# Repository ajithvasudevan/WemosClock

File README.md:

## Wemos Clock

This clock is based on the Wemos D1 Mini MCU and it keeps accurate time using NTP servers over the internet, just like regular computers.

### Schematic Diagram

### Parts List
1. 7-Segment Display units (2.3 inch high for this PCB design, otherwise, could be any size) - 4 Nos
2. Wemos D1 Mini - 1 No
3. General purpose NPN transistors (E.g., 2N 2222A)  - 11 Nos
4. General purpose PNP transistors (E.g., 2N 2907A)  - 4 Nos
5. Resistors - 2k2 Ω   - 21 Nos
6. Resistors - 220 Ω   -  7 Nos
7. 12V DC 5W Power supply module HLK-5M12 - 1 No
8. 5V Regulator IC 7805 - 1 No
9. Capacitor 470 μF  - No
10. PCB fabricated to the specifications [here](KiCAD/WemosClock.kicad_pcb)

### PCB

### PCB (3-D Model - component side)

### PCB (3-D Model - display side)

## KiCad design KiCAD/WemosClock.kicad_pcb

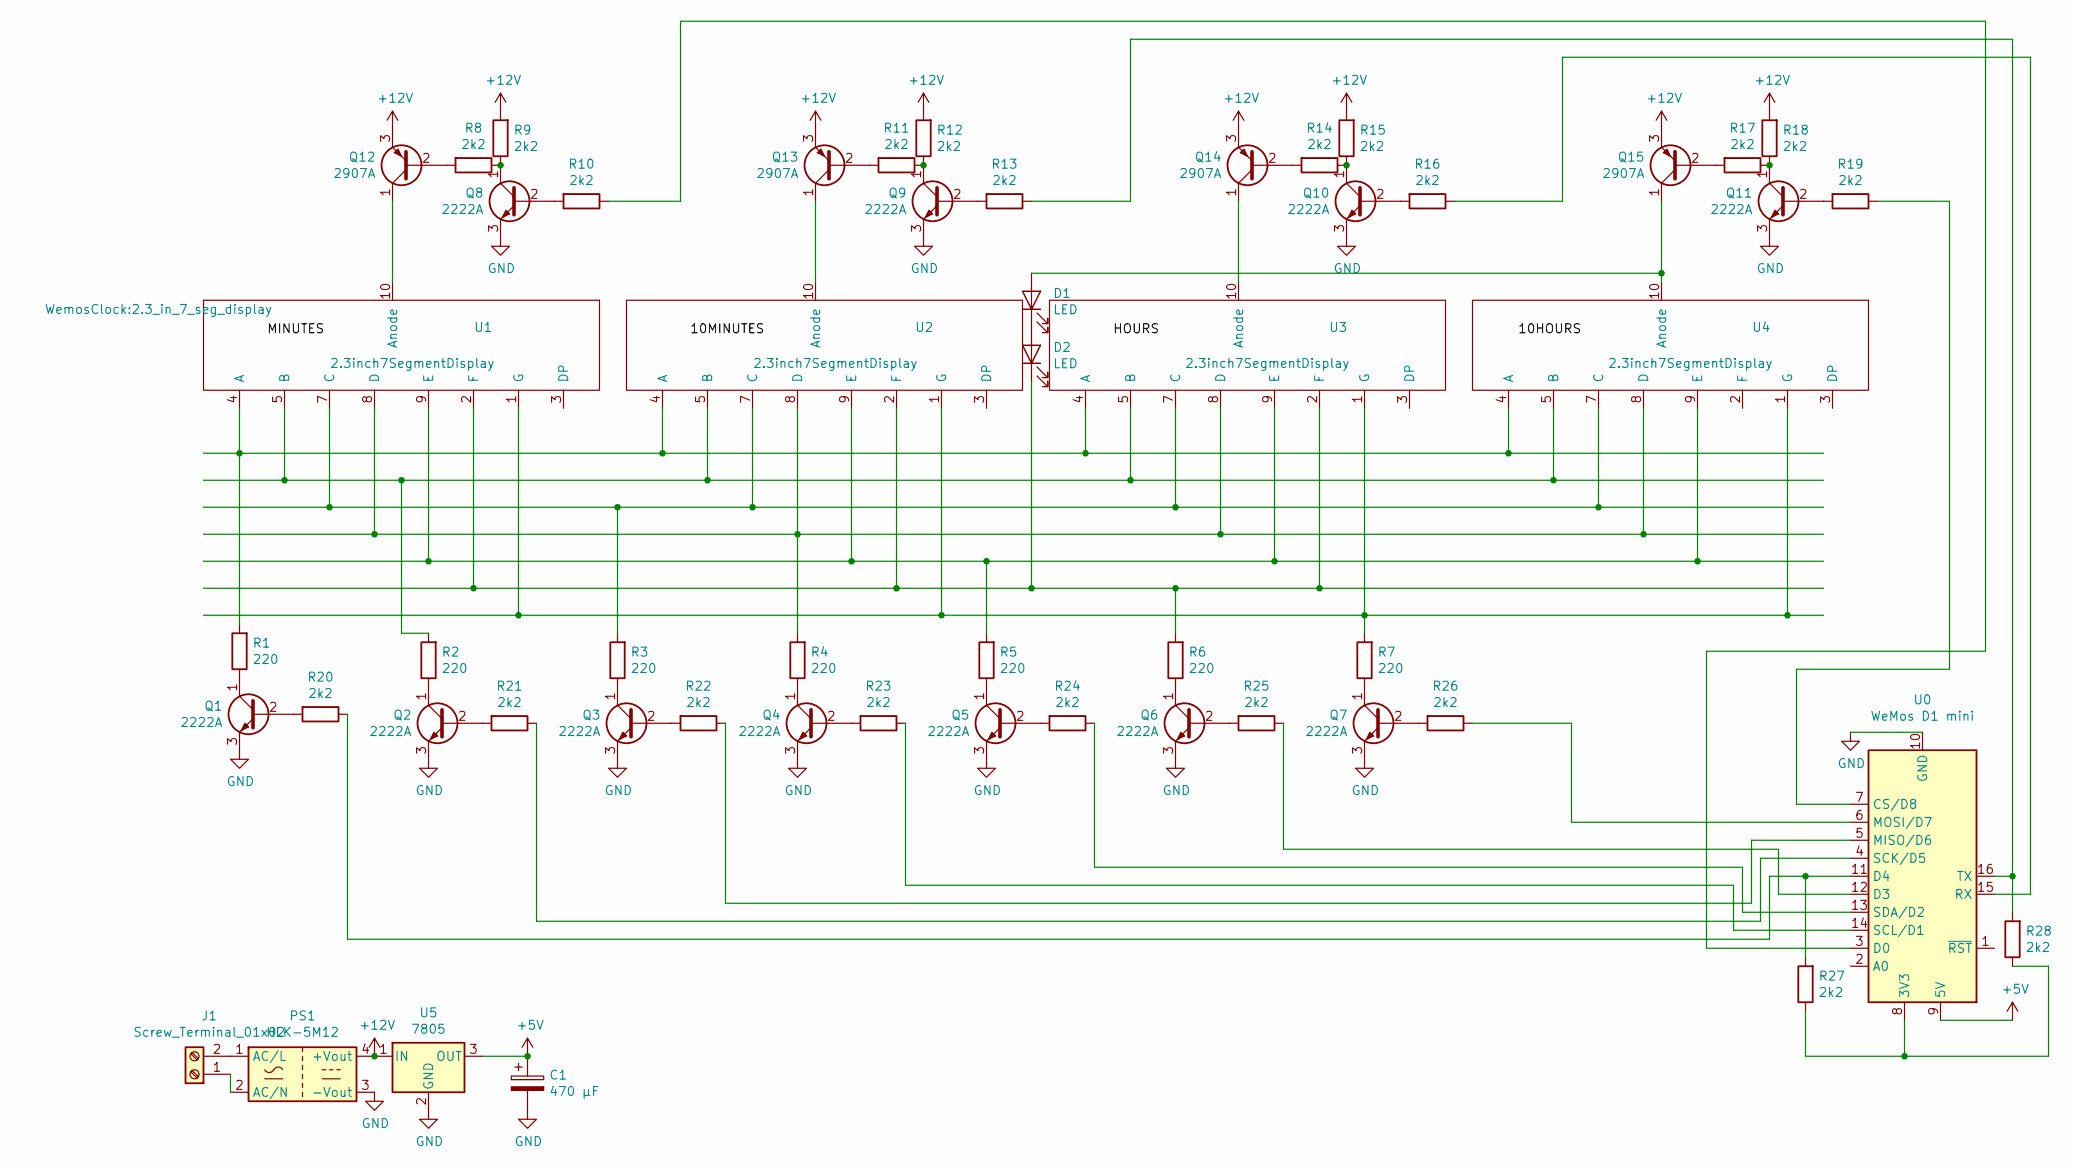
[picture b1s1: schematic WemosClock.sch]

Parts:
C1: 470 μF; CP_Radial_D10.0mm_P5.00mm
D1, D2: LED; LED_D5.0mm
J1: Screw_Terminal_01x02; TerminalBlock_bornier-2_P5.08mm
PS1: HLK-5M12
Q1, Q2, Q3, Q4, Q5, Q6, Q7, Q8, Q9, Q10, Q11: 2222A; TO-92L_Inline_Wide
Q12, Q13, Q14, Q15: 2907A; TO-92L_Inline_Wide
R1, R2, R3, R4, R5, R6, R7: 220; R_Axial_DIN0207_L6.3mm_D2.5mm_P10.16mm_Horizontal
R8, R9, R10, R11, R12, R13, R14, R15, R16, R17, R18, R19, R20, R21, R22, R23, R24, R25, R26, R27, R28: 2k2; R_Axial_DIN0207_L6.3mm_D2.5mm_P10.16mm_Horizontal
U0: WeMos D1 mini; WEMOS_D1_mini_3.0.0
U1, U2, U3, U4: 2.3inch7SegmentDisplay; 2.3_in_7_seg_display
U5: 7805; TO-220-3_Vertical

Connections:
+5V: C1.1, U0.9 (5V), U5.3 (OUT)
+12V: PS1.4 (+Vout), Q12.3 (E), Q13.3 (E), Q14.3 (E), Q15.3 (E), R9.2, R12.2, R15.2, R18.2, U5.1 (IN)
GND: C1.2, PS1.3 (-Vout), Q1.3 (E), Q2.3 (E), Q3.3 (E), Q4.3 (E), Q5.3 (E), Q6.3 (E), Q7.3 (E), Q8.3 (E), Q9.3 (E), Q10.3 (E), Q11.3 (E), U0.10 (GND), U5.2 (GND)
unnamed: D1.1 (K), D2.2 (A)
unnamed: D1.2 (A), Q15.1 (C), U4.10 (Anode)
unnamed: D2.1 (K), R6.2, U1.2 (F), U2.2 (F), U3.2 (F)
unnamed: J1.1, PS1.2 (AC/N)
unnamed: J1.2, PS1.1 (AC/L)
unnamed: Q1.1 (C), R1.1
unnamed: Q1.2 (B), R20.2
unnamed: Q2.1 (C), R2.1
unnamed: Q2.2 (B), R21.2
unnamed: Q3.1 (C), R3.1
unnamed: Q3.2 (B), R22.2
unnamed: Q4.1 (C), R4.1
unnamed: Q4.2 (B), R23.2
unnamed: Q5.1 (C), R5.1
unnamed: Q5.2 (B), R24.2
unnamed: Q6.1 (C), R6.1
unnamed: Q6.2 (B), R25.2
unnamed: Q7.1 (C), R7.1
unnamed: Q7.2 (B), R26.2
unnamed: Q8.1 (C), R8.1, R9.1
unnamed: Q8.2 (B), R10.2
unnamed: Q9.1 (C), R11.1, R12.1
unnamed: Q9.2 (B), R13.2
unnamed: Q10.1 (C), R14.1, R15.1
unnamed: Q10.2 (B), R16.2
unnamed: Q11.1 (C), R17.1, R18.1
unnamed: Q11.2 (B), R19.2
unnamed: Q12.1 (C), U1.10 (Anode)
unnamed: Q12.2 (B), R8.2
unnamed: Q13.1 (C), U2.10 (Anode)
unnamed: Q13.2 (B), R11.2
unnamed: Q14.1 (C), U3.10 (Anode)
unnamed: Q14.2 (B), R14.2
unnamed: Q15.2 (B), R17.2
unnamed: R1.2, U1.4 (A), U2.4 (A), U3.4 (A), U4.4 (A)
unnamed: R2.2, U1.5 (B), U2.5 (B), U3.5 (B), U4.5 (B)
unnamed: R3.2, U1.7 (C), U2.7 (C), U3.7 (C), U4.7 (C)
unnamed: R4.2, U1.8 (D), U2.8 (D), U3.8 (D), U4.8 (D)
unnamed: R5.2, U1.9 (E), U2.9 (E), U3.9 (E), U4.9 (E)
unnamed: R7.2, U1.1 (G), U2.1 (G), U3.1 (G), U4.1 (G)
unnamed: R10.1, U0.3 (D0)
unnamed: R13.1, R28.2, U0.16 (TX)
unnamed: R16.1, U0.15 (RX)
unnamed: R19.1, U0.7 (CS/D8)
unnamed: R20.1, R27.2, U0.11 (D4)
unnamed: R21.1, U0.4 (SCK/D5)
unnamed: R22.1, U0.5 (MISO/D6)
unnamed: R23.1, U0.14 (SCL/D1)
unnamed: R24.1, U0.13 (SDA/D2)
unnamed: R25.1, U0.12 (D3)
unnamed: R26.1, U0.6 (MOSI/D7)
unnamed: R27.1, R28.1, U0.8 (3V3)

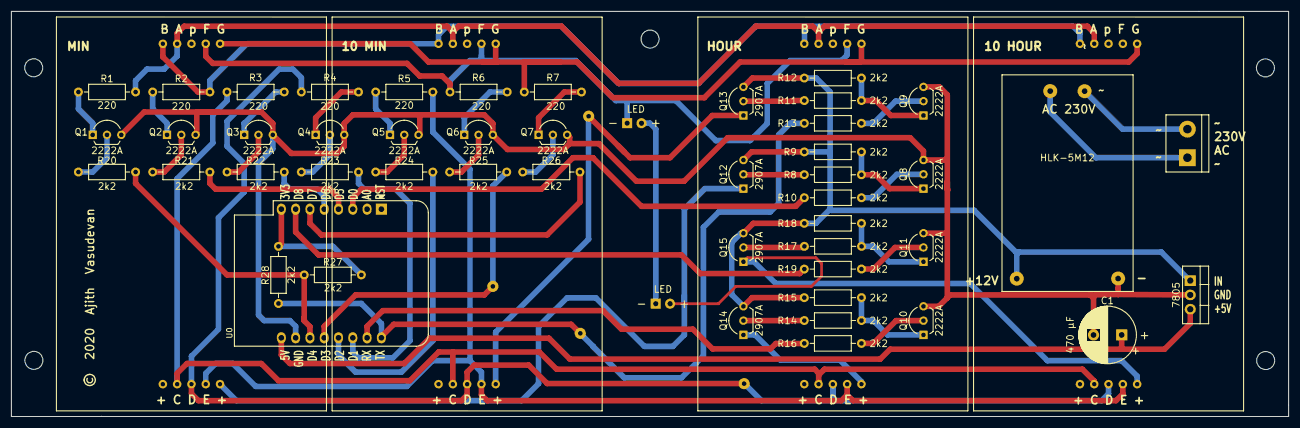
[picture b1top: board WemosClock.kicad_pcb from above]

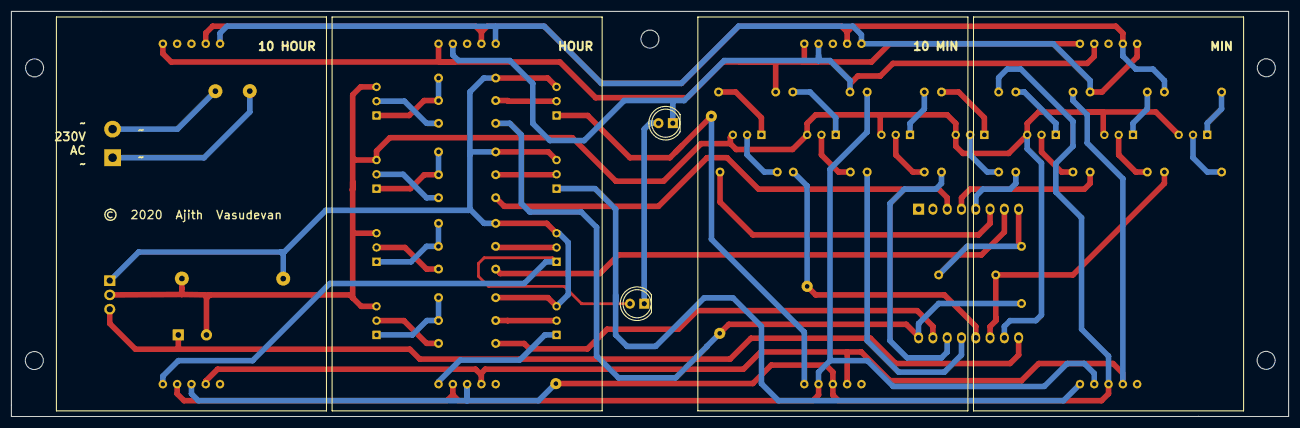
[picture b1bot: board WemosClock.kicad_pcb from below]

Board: 2 copper layers, 227.0 x 72.0 mm, 54 parts (6 on the bottom side), 55 nets.

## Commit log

2020-01-01 Removed commented code
2020-01-01 Updated Schematic png
2022-02-07 Added WemosClock-WifiManager.ino
    This version of the code uses WiFiManager to provide a user-friendly interface to setup WiFi SSID and Password

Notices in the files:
KiCAD/WemosClock.kicad_pcb:
©  2020  Ajith  Vasudevan
